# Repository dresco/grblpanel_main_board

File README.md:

# grblPANEL reference board

KiCad implementation of a grblPANEL control board, with the following features;
- up to 88 input keys
- up to 4 quadrature encoders
- display output (reference design using a 3.5" ILI9488 panel)
- Modbus and CAN bus (WIP) connectivity to grblHAL controller
- SWD connector (2x5 1.27mm) for programming and debugging
- USB C interface for programming and configuration (WIP)
- ESD protection on all user connections
- 5-12V DC power input - with reverse polarity, undervoltage, overvoltage, and overcurrent protection

The control board uses the following high level components;
- STM32G0 MCU running at 64MHz
- TI SN65HVD230 CAN transceiver
- TI THVD1406 Modbus transceiver
- Analog Devices ADP5589 I/O expander
- Analog Devices MAX17612A power protection IC

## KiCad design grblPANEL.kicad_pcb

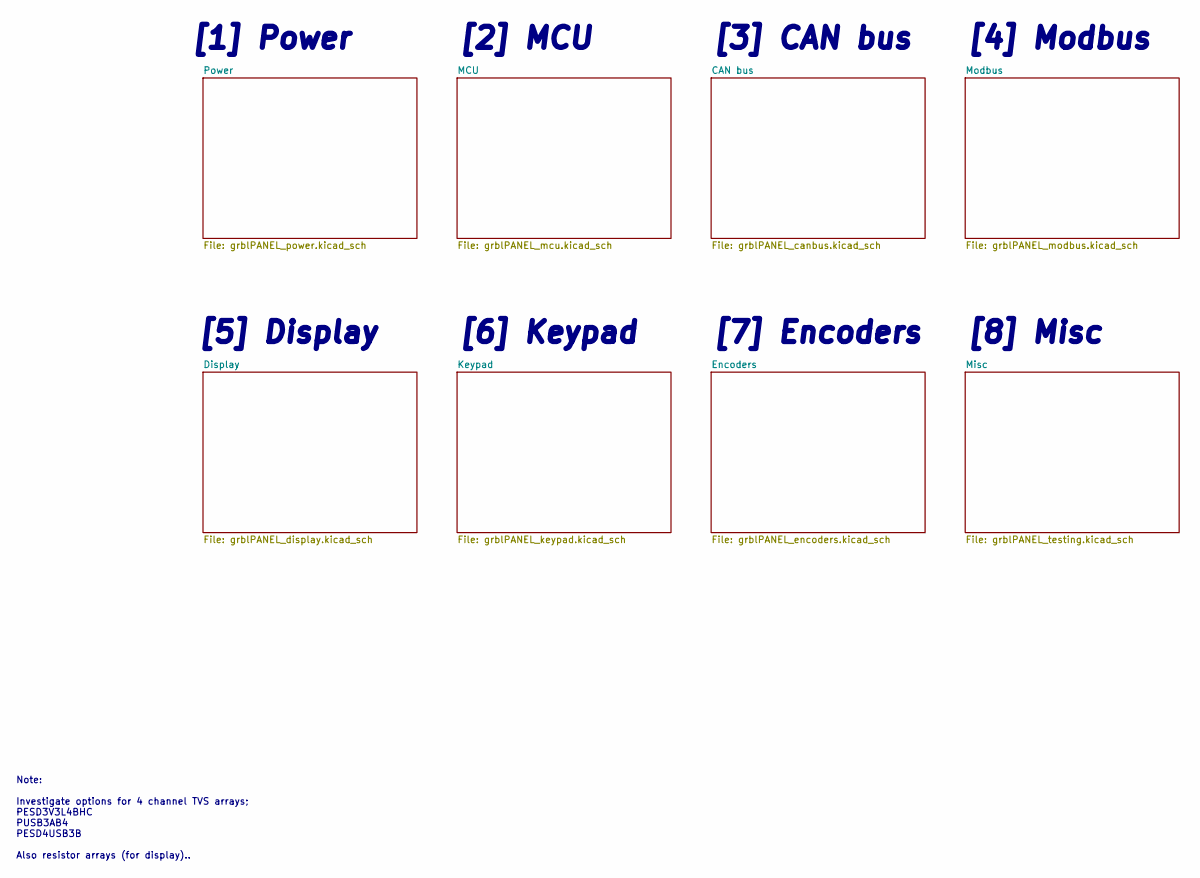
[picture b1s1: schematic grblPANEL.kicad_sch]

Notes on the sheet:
[2] MCU
[3] CAN bus
[1] Power
[8] Misc
Note: Investigate options for 4 channel TVS arrays; PESD3V3L4BHC PUSB3AB4 PESD4USB3B Also resistor arrays (for display)..
[6] Keypad
[4] Modbus
[5] Display
[7] Encoders

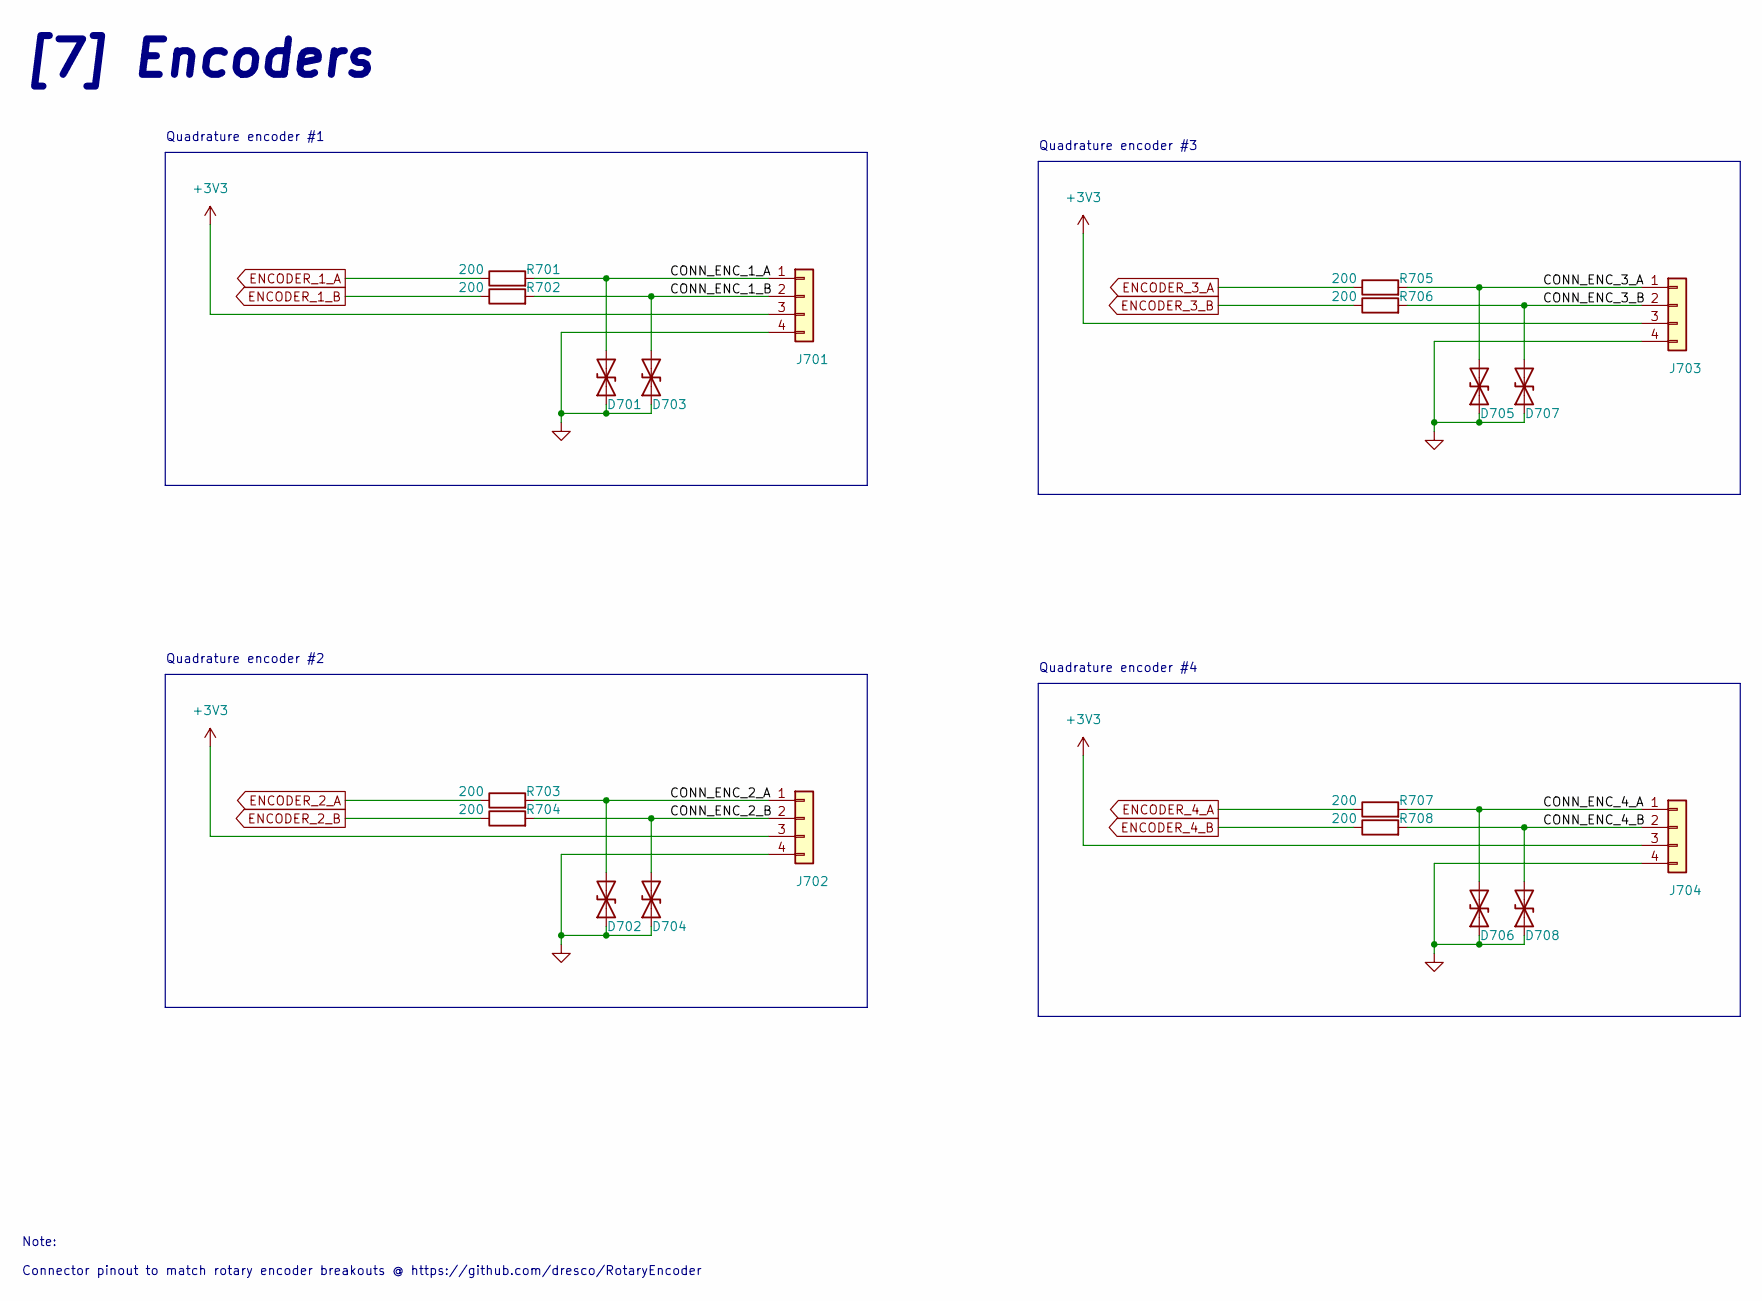
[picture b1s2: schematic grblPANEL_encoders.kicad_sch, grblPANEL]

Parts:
D701, D702, D703, D704, D705, D706, D707, D708: D_TVS; D_SOD-323
J701, J702, J703, J704: Conn_01x04; TerminalBlock_Phoenix_PT-1,5-4-3.5-H_1x04_P3.50mm_Horizontal
R701, R702, R703, R704, R705, R706, R707, R708: 200; R_0603_1608Metric

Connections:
+3V3: J701.3, J702.3, J703.3, J704.3; also elsewhere on the board
/Encoders/CONN_ENC_1_A: D701.2 (A2), J701.1, R701.2
/Encoders/CONN_ENC_1_B: D703.2 (A2), J701.2, R702.2
/Encoders/CONN_ENC_2_A: D702.2 (A2), J702.1, R703.2
/Encoders/CONN_ENC_2_B: D704.2 (A2), J702.2, R704.2
/Encoders/CONN_ENC_3_A: D705.2 (A2), J703.1, R705.2
/Encoders/CONN_ENC_3_B: D707.2 (A2), J703.2, R706.2
/Encoders/CONN_ENC_4_A: D706.2 (A2), J704.1, R707.2
/Encoders/CONN_ENC_4_B: D708.2 (A2), J704.2, R708.2
ENCODER_1_A: R701.1; also elsewhere on the board
ENCODER_1_B: R702.1; also elsewhere on the board
ENCODER_2_A: R703.1; also elsewhere on the board
ENCODER_2_B: R704.1; also elsewhere on the board
ENCODER_3_A: R705.1; also elsewhere on the board
ENCODER_3_B: R706.1; also elsewhere on the board
ENCODER_4_A: R707.1; also elsewhere on the board
ENCODER_4_B: R708.1; also elsewhere on the board
GND: D701.1 (A1), D702.1 (A1), D703.1 (A1), D704.1 (A1), D705.1 (A1), D706.1 (A1), D707.1 (A1), D708.1 (A1), J701.4, J702.4, J703.4, J704.4; also elsewhere on the board

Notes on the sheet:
Quadrature encoder #3
Quadrature encoder #1
[7] Encoders
Quadrature encoder #4
Quadrature encoder #2
Note: Connector pinout to match rotary encoder breakouts @ https://github.com/dresco/RotaryEncoder

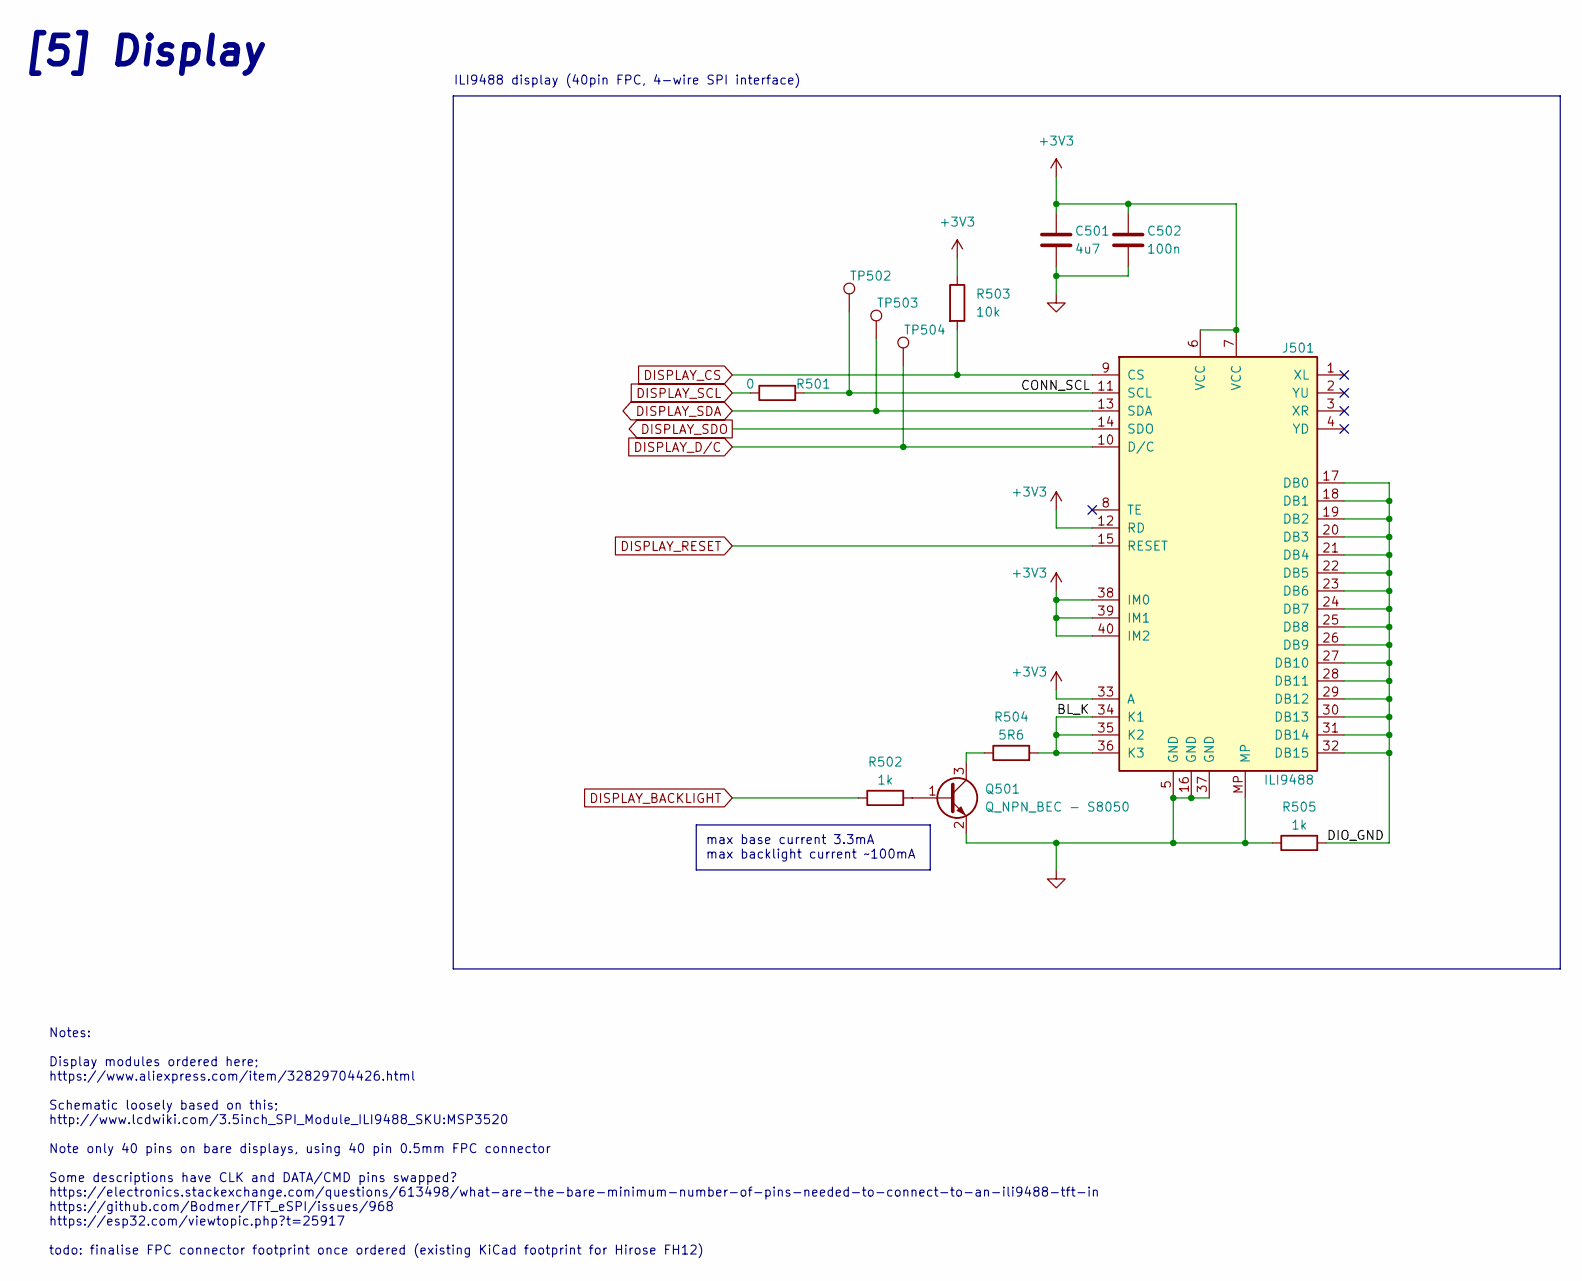
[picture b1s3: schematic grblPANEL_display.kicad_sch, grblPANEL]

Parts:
C501: 4u7; C_0805_2012Metric
C502: 100n; C_0603_1608Metric
J501: ILI9488; Hirose_FH12-40S-0.5SH_1x40-1MP_P0.50mm_Horizontal
Q501: Q_NPN_BEC - S8050; SOT-23
R501: 0; R_0603_1608Metric
R502, R505: 1k; R_0603_1608Metric
R503: 10k; R_0603_1608Metric
R504: 5R6; R_0603_1608Metric
TP502, TP503, TP504: TestPoint; TestPoint_THTPad_D2.0mm_Drill1.0mm

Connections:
+3V3: C501.1, C502.1, J501.6 (VCC), J501.7 (VCC), J501.12 (RD), J501.33 (A), J501.38 (IM0), J501.39 (IM1), J501.40 (IM2), R503.1; also elsewhere on the board
/Display/BL_K: J501.34 (K1), J501.35 (K2), J501.36 (K3), R504.2
/Display/CONN_SCL: J501.11 (SCL), R501.2, TP502.1
/Display/DIO_GND: J501.17 (DB0), J501.18 (DB1), J501.19 (DB2), J501.20 (DB3), J501.21 (DB4), J501.22 (DB5), J501.23 (DB6), J501.24 (DB7), J501.25 (DB8), J501.26 (DB9), J501.27 (DB10), J501.28 (DB11), J501.29 (DB12), J501.30 (DB13), J501.31 (DB14), J501.32 (DB15), R505.2
DISPLAY_BACKLIGHT: R502.1; also elsewhere on the board
DISPLAY_CS: J501.9 (CS), R503.2; also elsewhere on the board
DISPLAY_D/C: J501.10 (D/C), TP504.1; also elsewhere on the board
DISPLAY_RESET: J501.15 (RESET); also elsewhere on the board
DISPLAY_SCL: R501.1; also elsewhere on the board
DISPLAY_SDA: J501.13 (SDA), TP503.1; also elsewhere on the board
DISPLAY_SDO: J501.14 (SDO); also elsewhere on the board
GND: C501.2, C502.2, J501.5 (GND), J501.16 (GND), J501.37 (GND), J501.MP, Q501.2 (E), R505.1; also elsewhere on the board
unnamed: Q501.1 (B), R502.2
unnamed: Q501.3 (C), R504.1

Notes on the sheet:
[5] Display
max base current 3.3mA max backlight current ~100mA
Notes: Display modules ordered here; https://www.aliexpress.com/item/32829704426.html Schematic loosely based on this; http://www.lcdwiki.com/3.5inch_SPI_Module_ILI9488_SKU:MSP3520 Note only 40 pins on bare displays, using 40 pin 0.5mm FPC connector Some descriptions have CLK and DATA/CMD pins swap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
ILI9488 display (40pin FPC, 4-wire SPI interface)

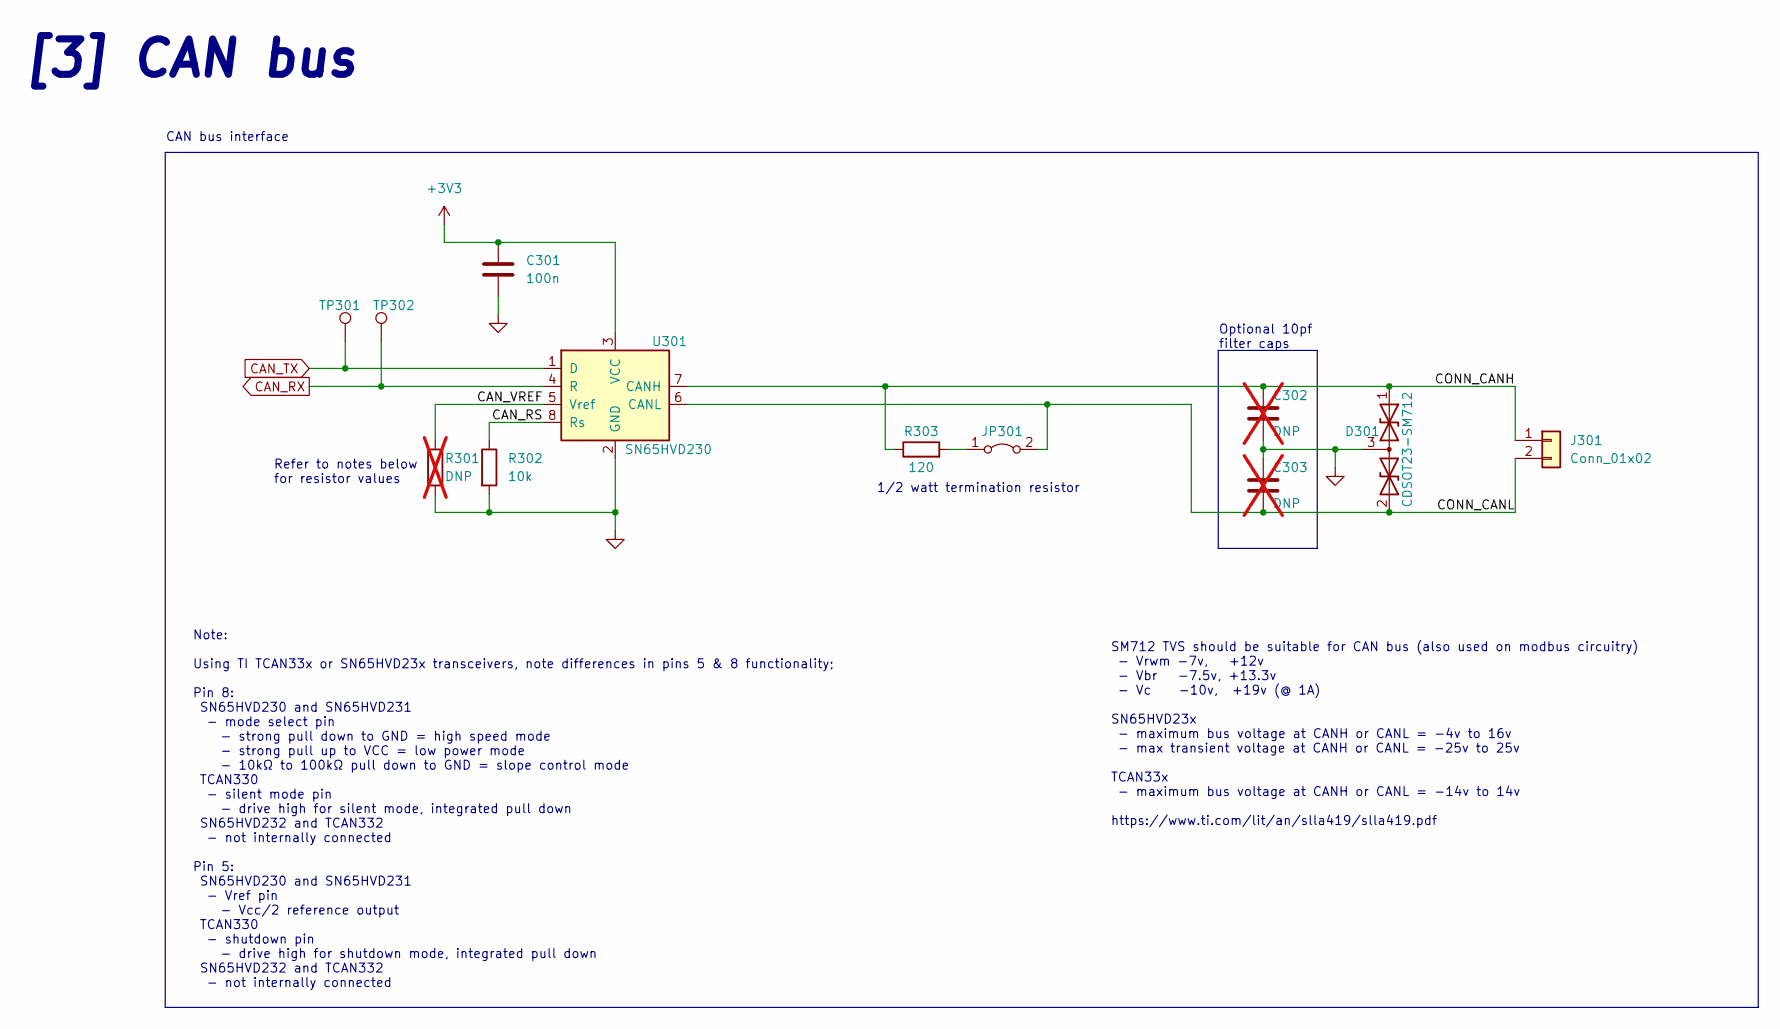
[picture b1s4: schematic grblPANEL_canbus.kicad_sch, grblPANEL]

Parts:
C301: 100n; C_0603_1608Metric
C302, C303: DNP; C_0603_1608Metric; not fitted
D301: CDSOT23-SM712; SOT-23
J301: Conn_01x02; TerminalBlock_Phoenix_PT-1,5-2-3.5-H_1x02_P3.50mm_Horizontal
JP301: Jumper_2_Bridged; PinHeader_1x02_P2.54mm_Vertical
R301: DNP; R_0603_1608Metric; not fitted
R302: 10k; R_0603_1608Metric
R303: 120; R_0603_1608Metric
TP301, TP302: TestPoint; TestPoint_THTPad_D2.0mm_Drill1.0mm
U301: SN65HVD230; SOIC-8_3.9x4.9mm_P1.27mm

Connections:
+3V3: C301.1, U301.3 (VCC); also elsewhere on the board
/CAN bus/CAN_RS: R302.1, U301.8 (Rs)
/CAN bus/CAN_VREF: R301.1, U301.5 (Vref)
/CAN bus/CONN_CANH: C302.1, D301.1 (A1), J301.1, R303.1, U301.7 (CANH)
/CAN bus/CONN_CANL: C303.2, D301.2 (A2), J301.2, JP301.2 (B), U301.6 (CANL)
CAN_RX: TP302.1, U301.4 (R); also elsewhere on the board
CAN_TX: TP301.1, U301.1 (D); also elsewhere on the board
GND: C301.2, C302.2, C303.1, D301.3 (common), R301.2, R302.2, U301.2 (GND); also elsewhere on the board
unnamed: JP301.1 (A), R303.2

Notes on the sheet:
Note: Using TI TCAN33x or SN65HVD23x transceivers, note differences in pins 5 & 8 functionality; Pin 8: SN65HVD230 and SN65HVD231 - mode select pin - strong pull down to GND = high speed mode - strong pull up to VCC = low power mode - 10kΩ to 100kΩ pull down to GND = slope control mode TCAN330 - si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
[3] CAN bus
CAN bus interface
SM712 TVS should be suitable for CAN bus (also used on modbus circuitry) - Vrwm -7v, +12v - Vbr -7.5v, +13.3v - Vc -10v, +19v (@ 1A) SN65HVD23x - maximum bus voltage at CANH or CANL = -4v to 16v - max transient voltage at CANH or CANL = -25v to 25v TCAN33x - maximum bus voltage at CANH or CANL = -1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
Refer to notes below for resistor values
1/2 watt termination resistor
Optional 10pf filter caps

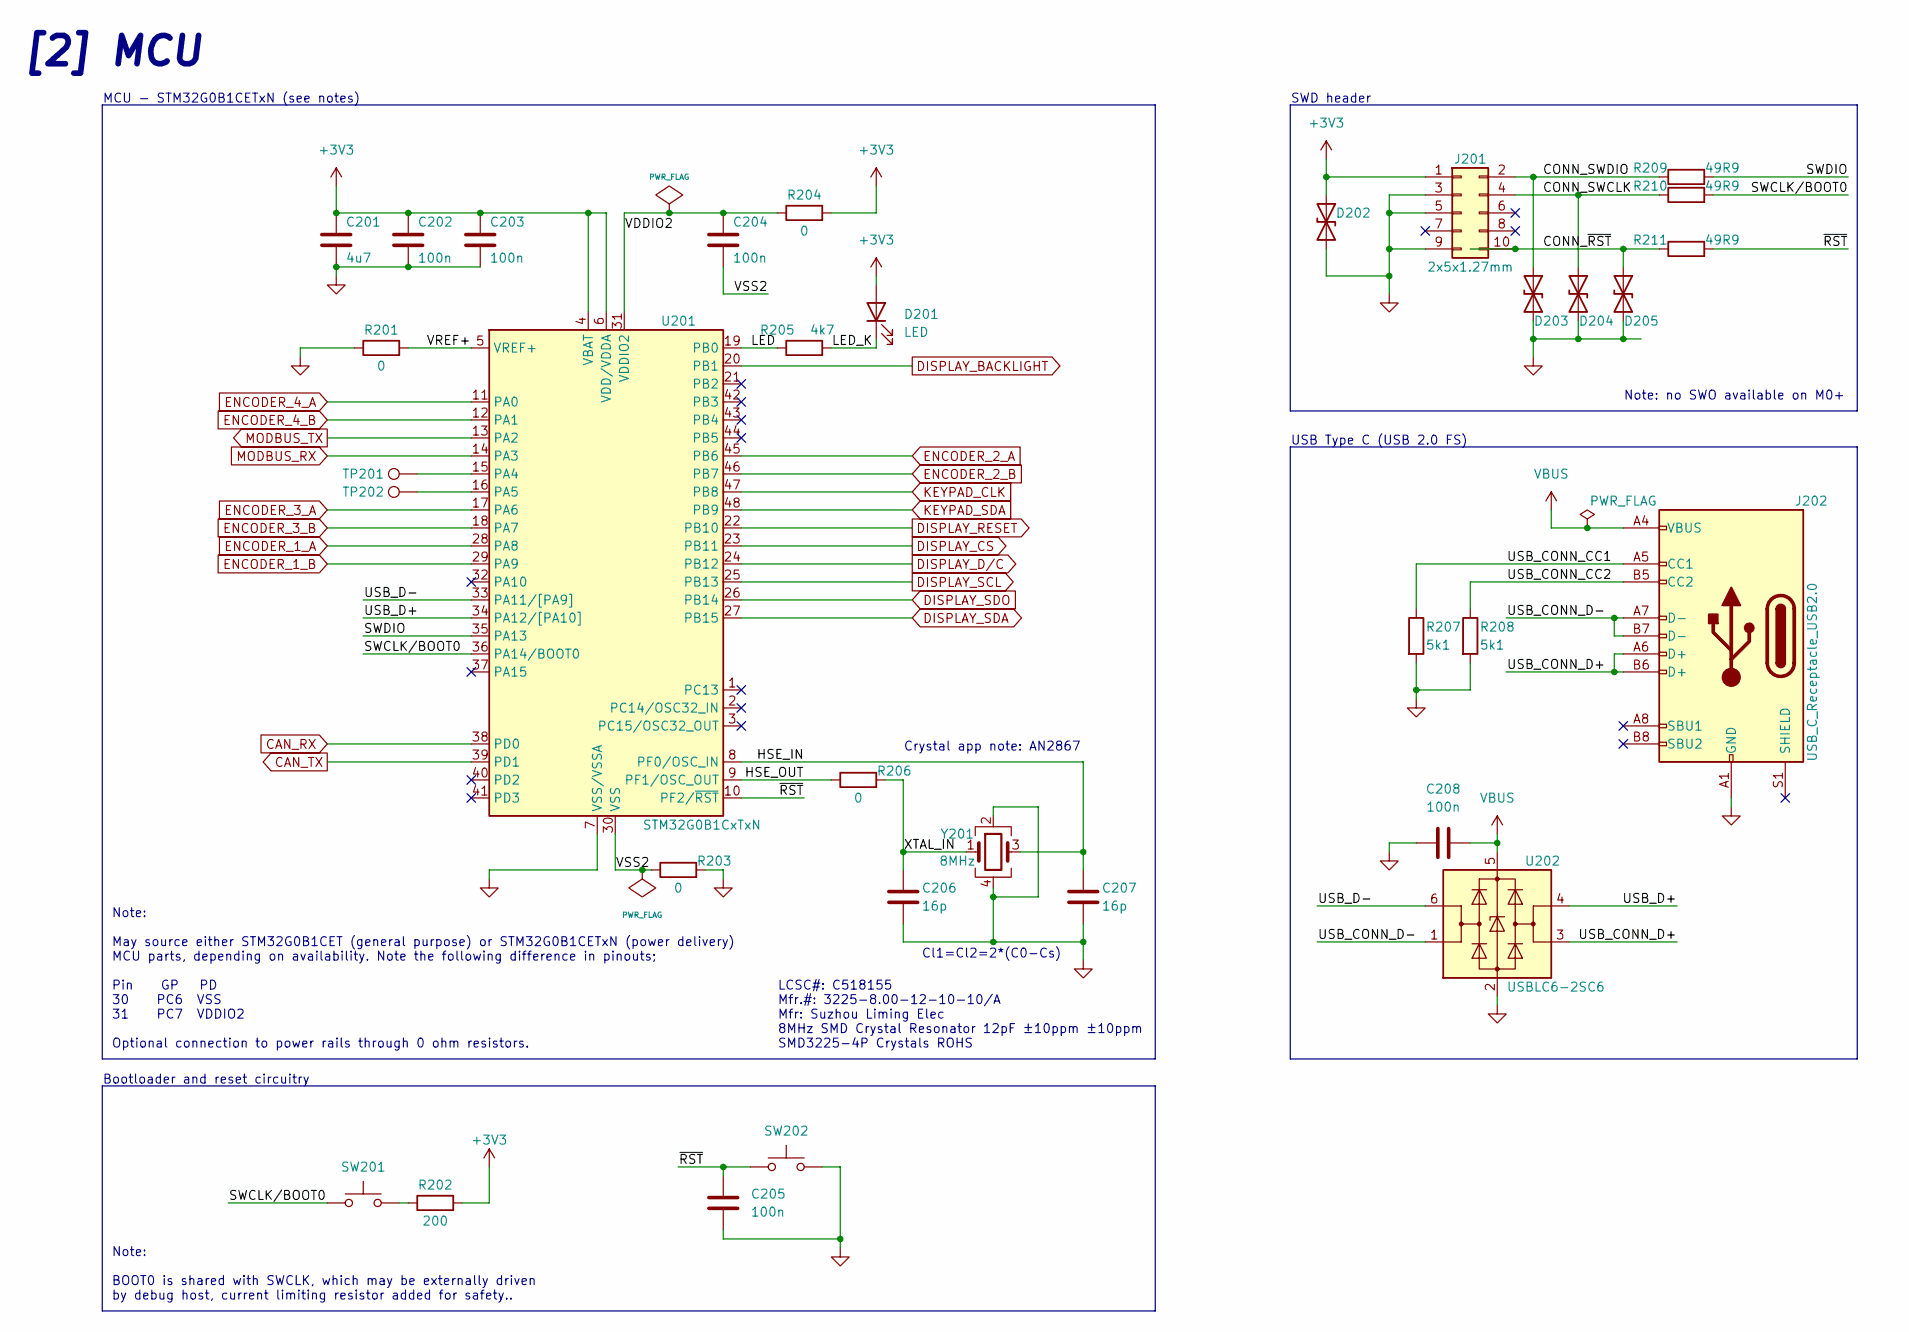
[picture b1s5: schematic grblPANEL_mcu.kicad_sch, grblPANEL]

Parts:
C201: 4u7; C_0805_2012Metric
C202, C203, C204, C205, C208: 100n; C_0603_1608Metric
C206, C207: 16p; C_0603_1608Metric
D201: LED; LED_0603_1608Metric
D202, D203, D204, D205: D_TVS; D_SOD-323
J201: 2x5x1.27mm; FTSH-105-01-L-DV-K
J202: USB_C_Receptacle_USB2.0; USB_C_Receptacle_HRO_TYPE-C-31-M-12
R201, R203, R204, R206: 0; R_0603_1608Metric
R202: 200; R_0603_1608Metric
R205: 4k7; R_0603_1608Metric
R207, R208: 5k1; R_0603_1608Metric
R209, R210, R211: 49R9; R_0603_1608Metric
SW201, SW202: SW_Push; SW_SPST_PTS810
TP201, TP202: TestPoint; TestPoint_THTPad_D2.0mm_Drill1.0mm
U201: STM32G0B1CxTxN; LQFP-48_7x7mm_P0.5mm
U202: USBLC6-2SC6; SOT-23-6
Y201: 8MHz; Crystal_SMD_3225-4Pin_3.2x2.5mm

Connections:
+3V3: C201.1, C202.1, C203.1, D201.2 (A), D202.1 (A1), J201.1, R202.2, R204.2, U201.4 (VBAT), U201.6 (VDD/VDDA); also elsewhere on the board
/MCU/CONN_SWCLK: D204.1 (A1), J201.4, R210.1
/MCU/CONN_SWDIO: D203.1 (A1), J201.2, R209.1
/MCU/CONN_~RST: D205.1 (A1), J201.10, R211.1
/MCU/HSE_IN: C207.1, U201.8 (PF0/OSC_IN), Y201.3
/MCU/HSE_OUT: R206.1, U201.9 (PF1/OSC_OUT)
/MCU/LED: R205.1, U201.19 (PB0)
/MCU/LED_K: D201.1 (K), R205.2
/MCU/SWCLK/BOOT0: R210.2, SW201.1, U201.36 (PA14/BOOT0)
/MCU/SWDIO: R209.2, U201.35 (PA13)
/MCU/USB_CONN_CC1: J202.A5 (CC1), R207.1
/MCU/USB_CONN_CC2: J202.B5 (CC2), R208.1
/MCU/USB_CONN_D+: J202.A6 (D+), J202.B6 (D+), U202.3 (I/O2)
/MCU/USB_CONN_D-: J202.A7 (D-), J202.B7 (D-), U202.1 (I/O1)
/MCU/USB_D+: U201.34 (PA12/[PA10]), U202.4 (I/O2)
/MCU/USB_D-: U201.33 (PA11/[PA9]), U202.6 (I/O1)
/MCU/VDDIO2: C204.1, R204.1, U201.31 (VDDIO2)
/MCU/VREF+: R201.2, U201.5 (VREF+)
/MCU/VSS2: C204.2, R203.1, U201.30 (VSS)
/MCU/XTAL_IN: C206.1, R206.2, Y201.1
/MCU/~RST: C205.1, R211.2, SW202.1, U201.10 (PF2/~RST)
CAN_RX: U201.38 (PD0); also elsewhere on the board
CAN_TX: U201.39 (PD1); also elsewhere on the board
DISPLAY_BACKLIGHT: U201.20 (PB1); also elsewhere on the board
DISPLAY_CS: U201.23 (PB11); also elsewhere on the board
DISPLAY_D/C: U201.24 (PB12); also elsewhere on the board
DISPLAY_RESET: U201.22 (PB10); also elsewhere on the board
DISPLAY_SCL: U201.25 (PB13); also elsewhere on the board
DISPLAY_SDA: U201.27 (PB15); also elsewhere on the board
DISPLAY_SDO: U201.26 (PB14); also elsewhere on the board
ENCODER_1_A: U201.28 (PA8); also elsewhere on the board
ENCODER_1_B: U201.29 (PA9); also elsewhere on the board
ENCODER_2_A: U201.45 (PB6); also elsewhere on the board
ENCODER_2_B: U201.46 (PB7); also elsewhere on the board
ENCODER_3_A: U201.17 (PA6); also elsewhere on the board
ENCODER_3_B: U201.18 (PA7); also elsewhere on the board
ENCODER_4_A: U201.11 (PA0); also elsewhere on the board
ENCODER_4_B: U201.12 (PA1); also elsewhere on the board
GND: C201.2, C202.2, C203.2, C205.2, C206.2, C207.2, C208.1, D202.2 (A2), D203.2 (A2), D204.2 (A2), D205.2 (A2), J201.3, J201.5, J201.9, J202.A1 (GND), J202.A12 (GND), J202.B1 (GND), J202.B12 (GND), R201.1, R203.2, R207.2, R208.2, SW202.2, U201.7 (VSS/VSSA), U202.2 (GND), Y201.2, Y201.4; also elsewhere on the board
KEYPAD_CLK: U201.47 (PB8); also elsewhere on the board
KEYPAD_SDA: U201.48 (PB9); also elsewhere on the board
MODBUS_RX: U201.14 (PA3); also elsewhere on the board
MODBUS_TX: U201.13 (PA2); also elsewhere on the board
unnamed: R202.1, SW201.2
unnamed: TP201.1, U201.15 (PA4)
unnamed: TP202.1, U201.16 (PA5)
VBUS: C208.2, J202.A4 (VBUS), J202.A9 (VBUS), J202.B4 (VBUS), J202.B9 (VBUS), U202.5 (VBUS); also elsewhere on the board

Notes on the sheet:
Note: BOOT0 is shared with SWCLK, which may be externally driven by debug host, current limiting resistor added for safety..
Cl1=Cl2=2*(C0-Cs)
Bootloader and reset circuitry
Crystal app note: AN2867
[2] MCU
MCU - STM32G0B1CETxN (see notes)
Note: May source either STM32G0B1CET (general purpose) or STM32G0B1CETxN (power delivery) MCU parts, depending on availability. Note the following difference in pinouts; Pin GP PD 30 PC6 VSS 31 PC7 VDDIO2 Optional connection to power rails through 0 ohm resistors.
LCSC#: C518155 Mfr.#: 3225-8.00-12-10-10/A Mfr: Suzhou Liming Elec 8MHz SMD Crystal Resonator 12pF ±10ppm ±10ppm SMD3225-4P Crystals ROHS
Note: no SWO available on M0+
USB Type C (USB 2.0 FS)
SWD header

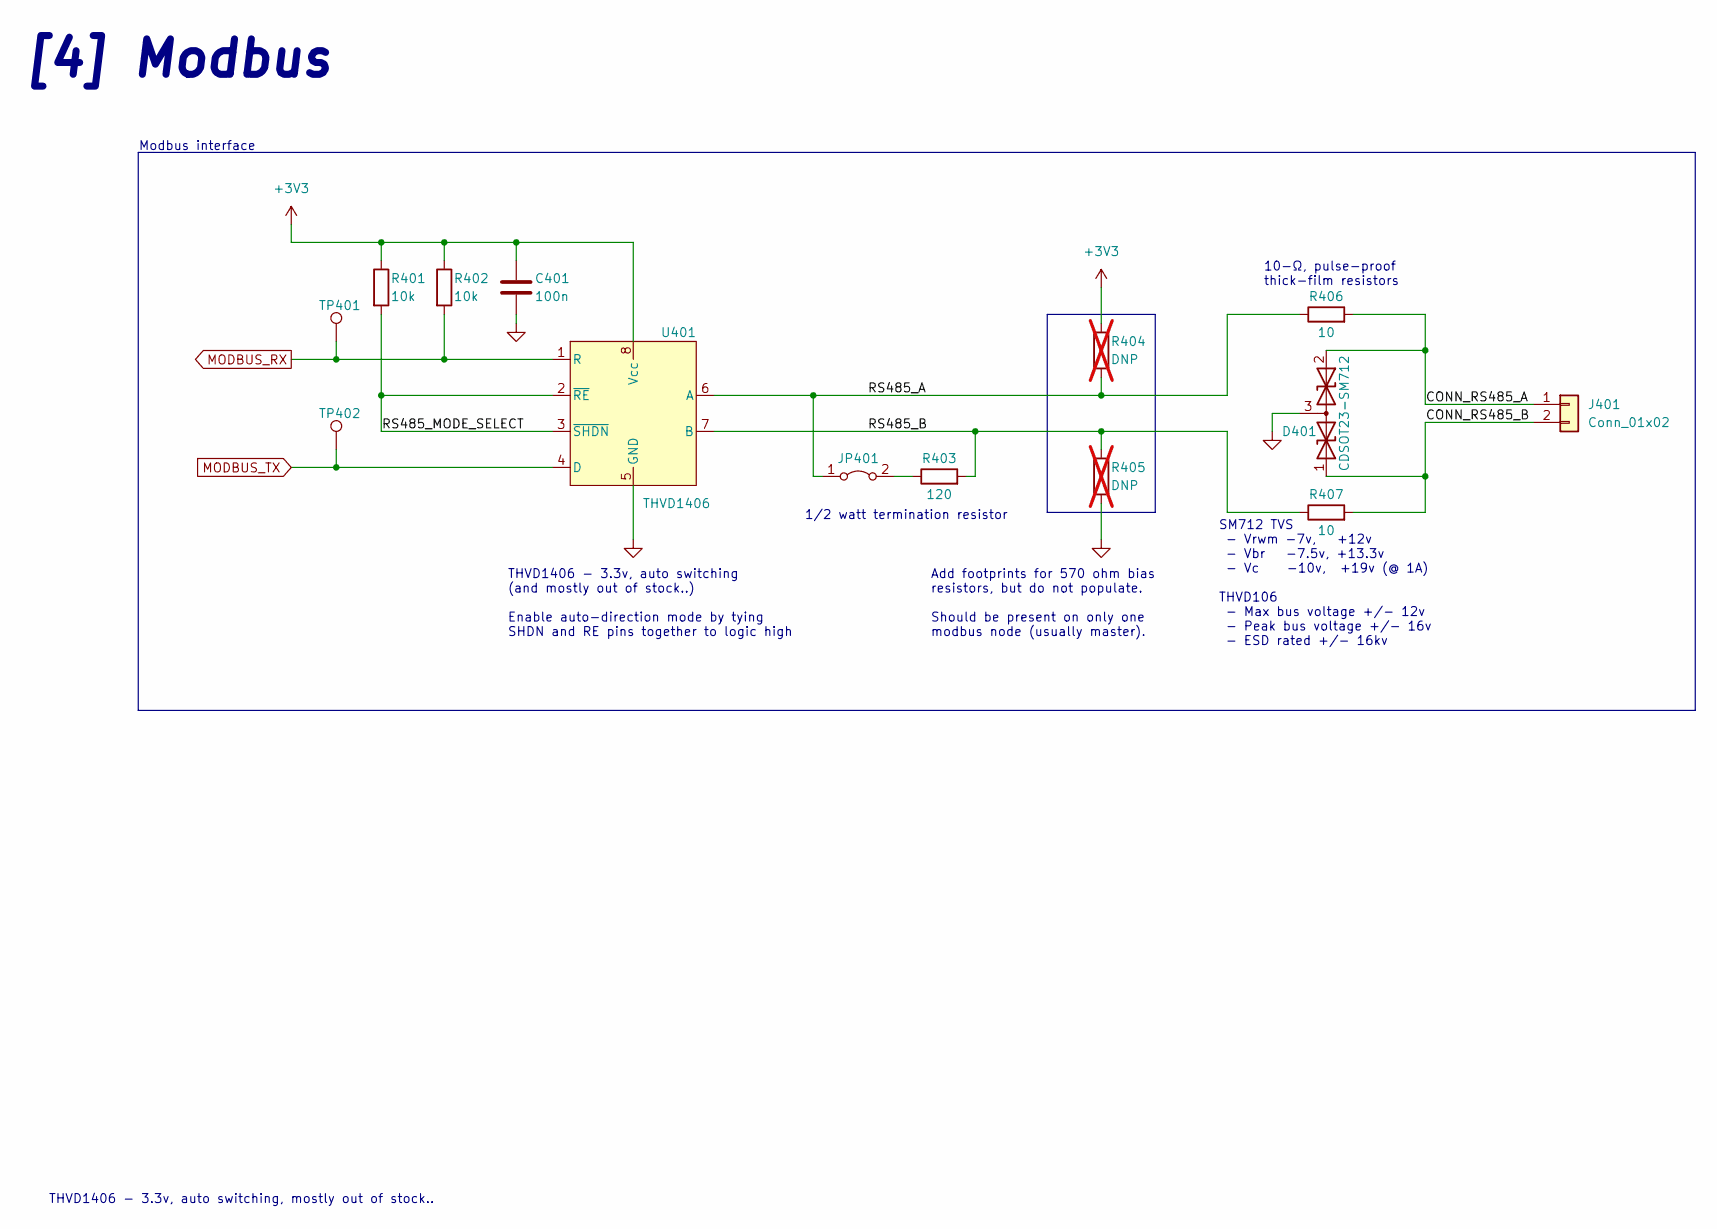
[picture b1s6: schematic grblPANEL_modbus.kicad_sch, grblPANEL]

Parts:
C401: 100n; C_0603_1608Metric
D401: CDSOT23-SM712; SOT-23
J401: Conn_01x02; TerminalBlock_Phoenix_PT-1,5-2-3.5-H_1x02_P3.50mm_Horizontal
JP401: Jumper_2_Bridged; PinHeader_1x02_P2.54mm_Vertical
R401, R402: 10k; R_0603_1608Metric
R403: 120; R_0603_1608Metric
R404, R405: DNP; R_0603_1608Metric; not fitted
R406, R407: 10; R_1206_3216Metric
TP401, TP402: TestPoint; TestPoint_THTPad_D2.0mm_Drill1.0mm
U401: THVD1406; SOIC-8_3.9x4.9mm_P1.27mm

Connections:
+3V3: C401.1, R401.1, R402.1, R404.1, U401.8 (Vcc); also elsewhere on the board
/Modbus/CONN_RS485_A: D401.2 (A2), J401.1, R406.2
/Modbus/CONN_RS485_B: D401.1 (A1), J401.2, R407.2
/Modbus/RS485_A: JP401.1 (A), R404.2, R406.1, U401.6 (A)
/Modbus/RS485_B: R403.2, R405.1, R407.1, U401.7 (B)
/Modbus/RS485_MODE_SELECT: R401.2, U401.2 (~RE), U401.3 (~SHDN)
GND: C401.2, D401.3 (common), R405.2, U401.5 (GND); also elsewhere on the board
MODBUS_RX: R402.2, TP401.1, U401.1 (R); also elsewhere on the board
MODBUS_TX: TP402.1, U401.4 (D); also elsewhere on the board
unnamed: JP401.2 (B), R403.1

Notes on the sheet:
THVD1406 - 3.3v, auto switching (and mostly out of stock..) Enable auto-direction mode by tying SHDN and RE pins together to logic high
[4] Modbus
Modbus interface
THVD1406 - 3.3v, auto switching, mostly out of stock..
Add footprints for 570 ohm bias resistors, but do not populate. Should be present on only one modbus node (usually master).
SM712 TVS - Vrwm -7v, +12v - Vbr -7.5v, +13.3v - Vc -10v, +19v (@ 1A) THVD106 - Max bus voltage +/- 12v - Peak bus voltage +/- 16v - ESD rated +/- 16kv
1/2 watt termination resistor
10-Ω, pulse-proof thick-film resistors

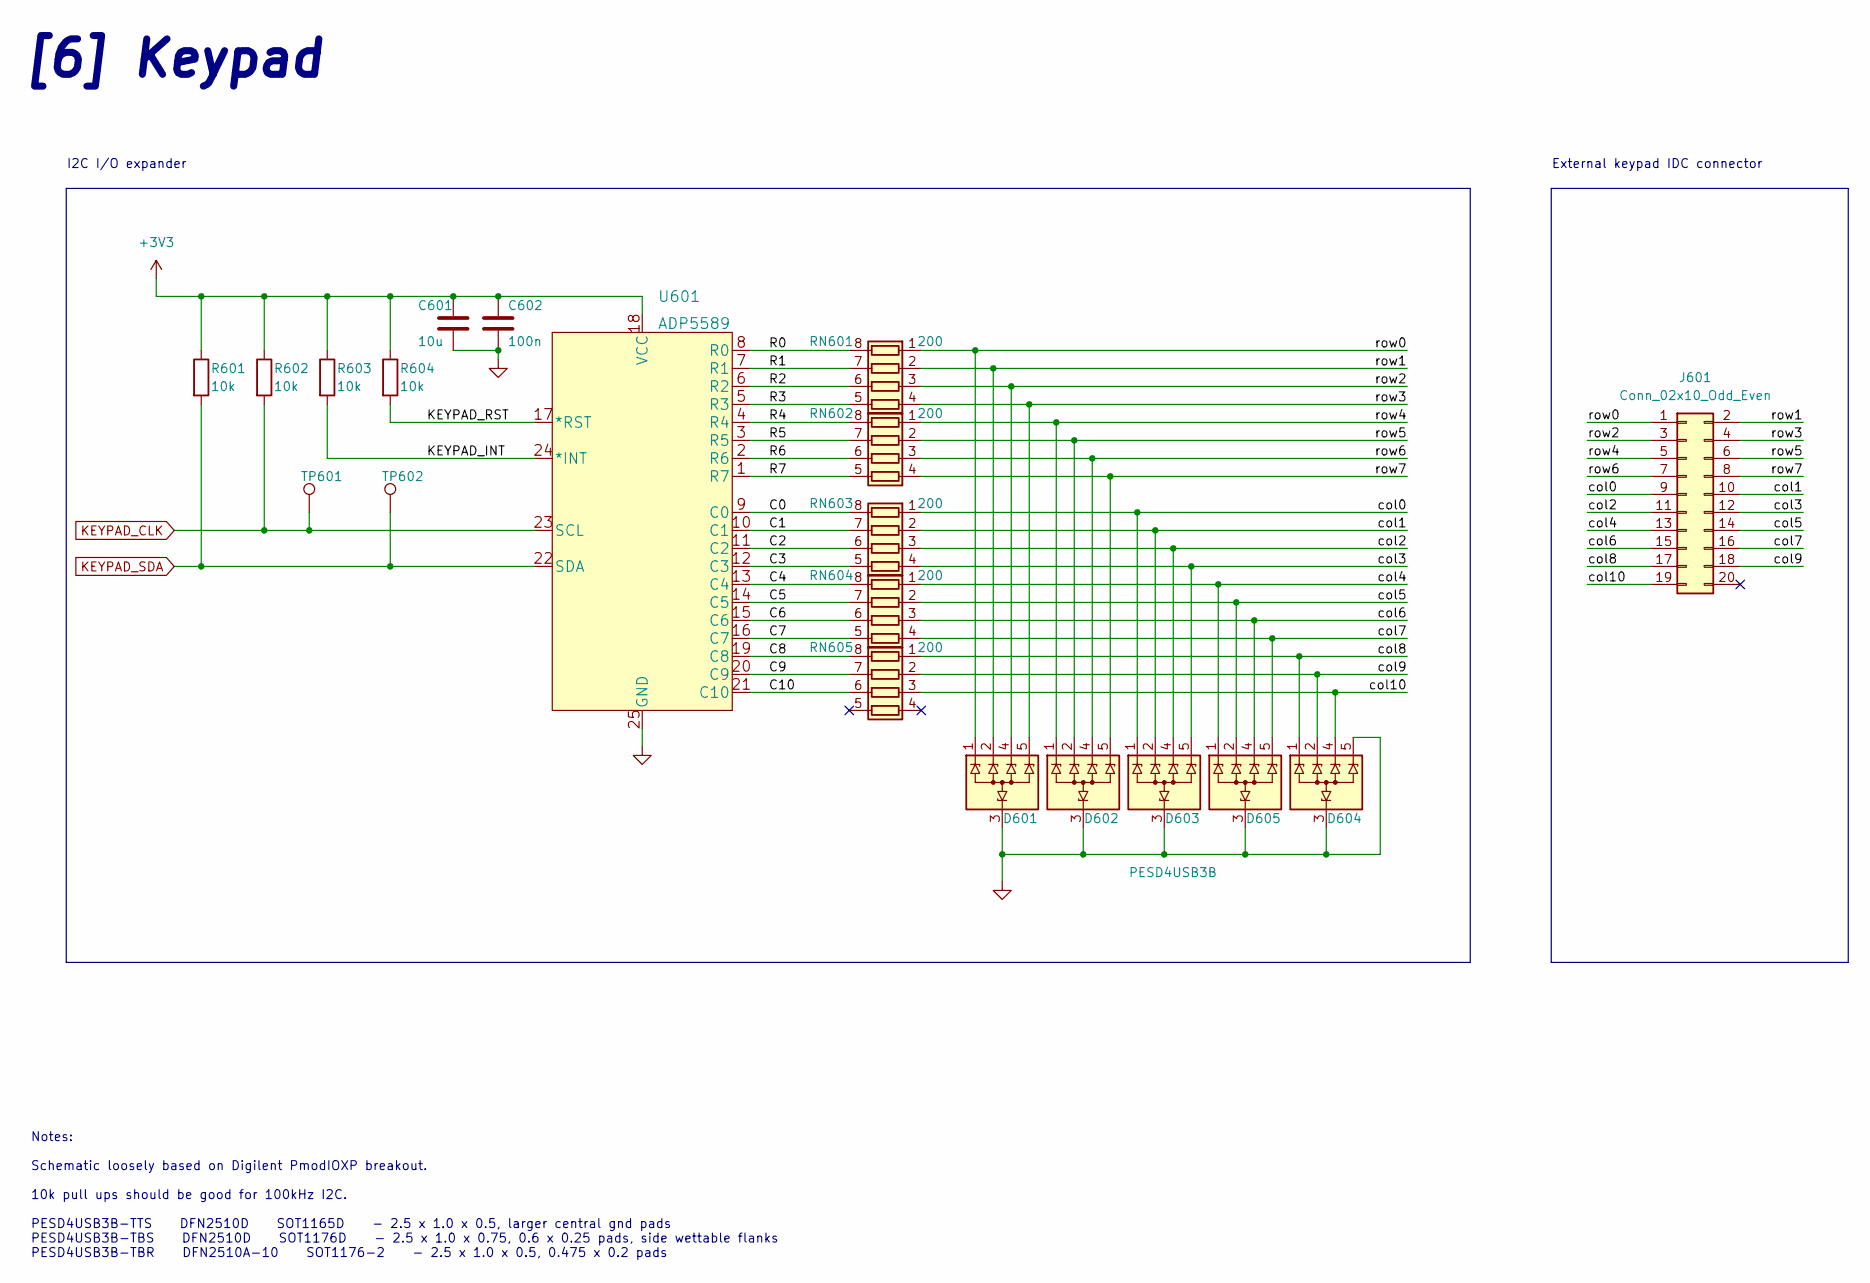
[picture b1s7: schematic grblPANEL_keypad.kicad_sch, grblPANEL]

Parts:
C601: 10u; C_0805_2012Metric
C602: 100n; C_0603_1608Metric
D601, D602, D603, D604, D605: PESD4USB3B; SOT1176D
J601: Conn_02x10_Odd_Even; IDC-Header_2x10_P2.54mm_Vertical
R601, R602, R603, R604: 10k; R_0603_1608Metric
RN601, RN602, RN603, RN604, RN605: 200; R_Array_Convex_4x0603
TP601, TP602: TestPoint; TestPoint_THTPad_D2.0mm_Drill1.0mm
U601: ADP5589; LFCSP-24-1EP_3.5x3.5mm_P0.4mm_EP2.2x2.2mm_ThermalVias

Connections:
+3V3: C601.1, C602.1, R601.1, R602.1, R603.1, R604.1, U601.18 (VCC); also elsewhere on the board
/Keypad/C0: RN603.8 (R1.2), U601.9 (C0)
/Keypad/C1: RN603.7 (R2.2), U601.10 (C1)
/Keypad/C2: RN603.6 (R3.2), U601.11 (C2)
/Keypad/C3: RN603.5 (R4.2), U601.12 (C3)
/Keypad/C4: RN604.8 (R1.2), U601.13 (C4)
/Keypad/C5: RN604.7 (R2.2), U601.14 (C5)
/Keypad/C6: RN604.6 (R3.2), U601.15 (C6)
/Keypad/C7: RN604.5 (R4.2), U601.16 (C7)
/Keypad/C8: RN605.8 (R1.2), U601.19 (C8)
/Keypad/C9: RN605.7 (R2.2), U601.20 (C9)
/Keypad/C10: RN605.6 (R3.2), U601.21 (C10)
/Keypad/KEYPAD_INT: R603.2, U601.24 (*INT)
/Keypad/KEYPAD_RST: R604.2, U601.17 (*RST)
/Keypad/R0: RN601.8 (R1.2), U601.8 (R0)
/Keypad/R1: RN601.7 (R2.2), U601.7 (R1)
/Keypad/R2: RN601.6 (R3.2), U601.6 (R2)
/Keypad/R3: RN601.5 (R4.2), U601.5 (R3)
/Keypad/R4: RN602.8 (R1.2), U601.4 (R4)
/Keypad/R5: RN602.7 (R2.2), U601.3 (R5)
/Keypad/R6: RN602.6 (R3.2), U601.2 (R6)
/Keypad/R7: RN602.5 (R4.2), U601.1 (R7)
/Keypad/col0: D603.1 (TVS1), D603.10 (TVS1), J601.9, RN603.1 (R1.1)
/Keypad/col1: D603.2 (TVS2), D603.9 (TVS2), J601.10, RN603.2 (R2.1)
/Keypad/col2: D603.4 (TVS3), D603.7 (TVS3), J601.11, RN603.3 (R3.1)
/Keypad/col3: D603.5 (TVS4), D603.6 (TVS4), J601.12, RN603.4 (R4.1)
/Keypad/col4: D604.1 (TVS1), D604.10 (TVS1), J601.13, RN604.1 (R1.1)
/Keypad/col5: D604.2 (TVS2), D604.9 (TVS2), J601.14, RN604.2 (R2.1)
/Keypad/col6: D604.4 (TVS3), D604.7 (TVS3), J601.15, RN604.3 (R3.1)
/Keypad/col7: D604.5 (TVS4), D604.6 (TVS4), J601.16, RN604.4 (R4.1)
/Keypad/col8: D605.1 (TVS1), D605.10 (TVS1), J601.17, RN605.1 (R1.1)
/Keypad/col9: D605.2 (TVS2), D605.9 (TVS2), J601.18, RN605.2 (R2.1)
/Keypad/col10: D605.4 (TVS3), D605.7 (TVS3), J601.19, RN605.3 (R3.1)
/Keypad/row0: D601.1 (TVS1), D601.10 (TVS1), J601.1, RN601.1 (R1.1)
/Keypad/row1: D601.2 (TVS2), D601.9 (TVS2), J601.2, RN601.2 (R2.1)
/Keypad/row2: D601.4 (TVS3), D601.7 (TVS3), J601.3, RN601.3 (R3.1)
/Keypad/row3: D601.5 (TVS4), D601.6 (TVS4), J601.4, RN601.4 (R4.1)
/Keypad/row4: D602.1 (TVS1), D602.10 (TVS1), J601.5, RN602.1 (R1.1)
/Keypad/row5: D602.2 (TVS2), D602.9 (TVS2), J601.6, RN602.2 (R2.1)
/Keypad/row6: D602.4 (TVS3), D602.7 (TVS3), J601.7, RN602.3 (R3.1)
/Keypad/row7: D602.5 (TVS4), D602.6 (TVS4), J601.8, RN602.4 (R4.1)
GND: C601.2, C602.2, D601.3 (GND), D601.8 (GND), D602.3 (GND), D602.8 (GND), D603.3 (GND), D603.8 (GND), D604.3 (GND), D604.8 (GND), D605.3 (GND), D605.5 (TVS4), D605.6 (TVS4), D605.8 (GND), U601.25 (GND); also elsewhere on the board
KEYPAD_CLK: R602.2, TP601.1, U601.23 (SCL); also elsewhere on the board
KEYPAD_SDA: R601.2, TP602.1, U601.22 (SDA); also elsewhere on the board

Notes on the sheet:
I2C I/O expander
[6] Keypad
External keypad IDC connector
Notes: Schematic loosely based on Digilent PmodIOXP breakout. 10k pull ups should be good for 100kHz I2C. PESD4USB3B-TTS DFN2510D SOT1165D - 2.5 x 1.0 x 0.5, larger central gnd pads PESD4USB3B-TBS DFN2510D SOT1176D - 2.5 x 1.0 x 0.75, 0.6 x 0.25 pads, side wettable flanks PESD4USB3B-TBR DFN2510A-10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

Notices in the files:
grblPANEL.kicad_pcb:
CC-BY-SA
